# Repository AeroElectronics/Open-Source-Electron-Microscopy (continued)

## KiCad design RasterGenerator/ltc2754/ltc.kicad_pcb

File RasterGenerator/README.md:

The raster generator is based on the LTC2754. It is a quad channel multiplying current output DAC with impressive specifications. My (as of yet untested) idea is to use two of the channels to create raster patterns and use the other two channels to attenuate those signals using the multiplying functionality. Ideally, this should provide attenuation and improve dynamic range, but it remains to be seen how well this will work, especially at high speeds. More to come.

I would hole off on trying to replicate this work until I spend some more time seeing if its going to work well.

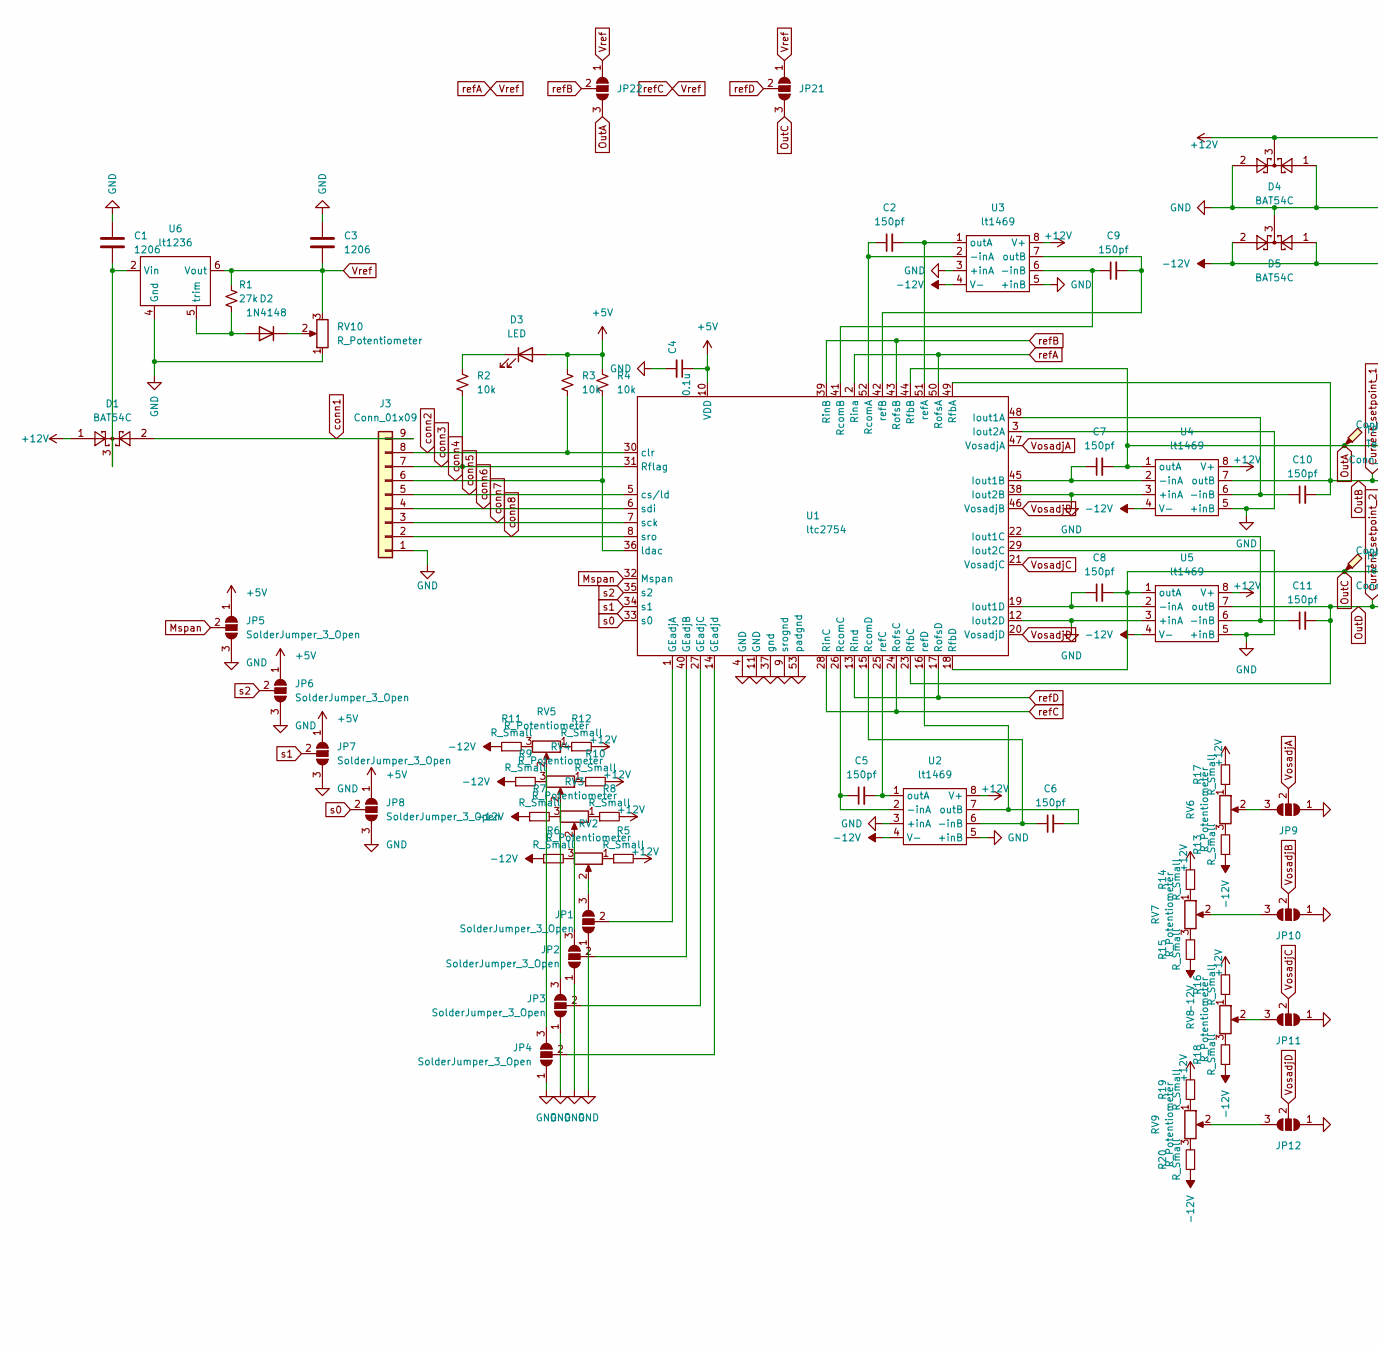
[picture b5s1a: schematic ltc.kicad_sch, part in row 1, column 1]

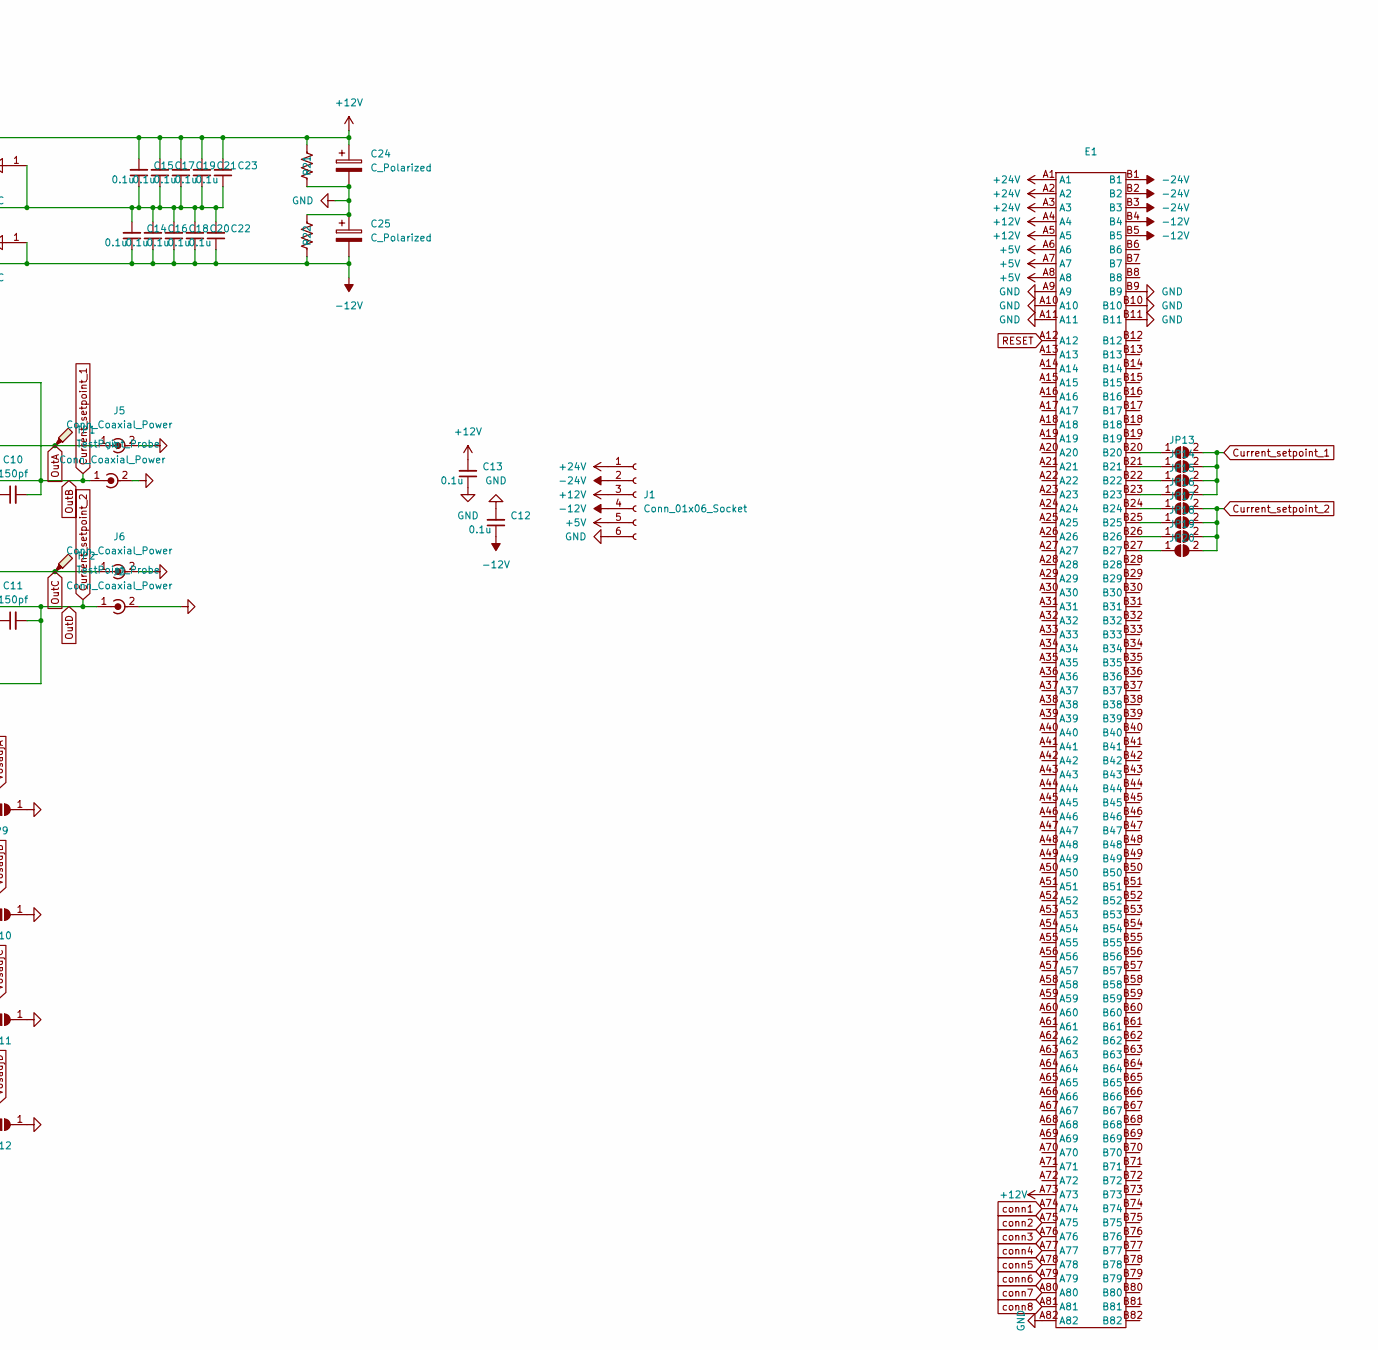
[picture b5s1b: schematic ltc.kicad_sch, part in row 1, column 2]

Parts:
C1, C3: 1206; C_1206_3216Metric
C2, C5, C6, C7, C8, C9, C10, C11: 150pf; C_0603_1608Metric_Pad1.08x0.95mm_HandSolder
C4, C12, C13, C14, C15, C16, C17, C18, C19, C20, C21, C22, C23: 0.1u; C_1206_3216Metric
C24, C25: C_Polarized; CP_Radial_D10.0mm_P5.00mm
D1, D4, D5: BAT54C; SOT-23
D2: 1N4148; D_SOD-323_HandSoldering
D3: LED; LED_0201_0603Metric_Pad0.64x0.40mm_HandSolder
E1: BUS_PCIexpress_x16
J1: Conn_01x06_Socket; PhoenixContact_MC_1,5_6-GF-3.81_1x06_P3.81mm_Horizontal_Thr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
J2, J4: Conn_Coaxial_Power; BNC_Amphenol_B6252HB-NPP3G-50_Horizontal
J3: Conn_01x09; PinHeader_1x09_P2.54mm_Vertical
J5, J6: Conn_Coaxial_Power; U.FL_Molex_MCRF_73412-0110_Vertical
JP1, JP2, JP3, JP4, JP5, JP6, JP7, JP8, JP9, JP10, JP11, JP12, JP21, JP22: SolderJumper_3_Open; SolderJumper-3_P1.3mm_Open_RoundedPad1.0x1.5mm
JP13, JP14, JP15, JP16, JP17, JP18, JP19, JP20: SolderJumper_2_Open; SolderJumper-2_P1.3mm_Open_RoundedPad1.0x1.5mm
R1: 27k; R_0603_1608Metric_Pad0.98x0.95mm_HandSolder
R2, R3, R4: 10k; R_0603_1608Metric_Pad0.98x0.95mm_HandSolder
R5, R6, R7, R8, R9, R10, R11, R12, R13, R14, R15, R16, R17, R18, R19, R20: R_Small; R_0603_1608Metric_Pad0.98x0.95mm_HandSolder
R21, R22: 100k; R_0603_1608Metric_Pad0.98x0.95mm_HandSolder
RV2, RV3, RV4, RV5, RV6, RV7, RV8, RV9, RV10: R_Potentiometer; Potentiometer_Bourns_3296W_Vertical
TP1, TP2: TestPoint_Probe; PinHeader_1x01_P2.54mm_Vertical
U1: ltc2754; LTC2754BCUKG-16-PBF
U2, U3, U4, U5: lt1469; LT1469IS8-PBF
U6: lt1236; SOIC-8_3.9x4.9mm_P1.27mm

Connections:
+5V: C4.1, D3.2 (A), E1.A6, E1.A7, E1.A8, J1.5, JP5.1 (A), JP6.1 (A), JP7.1 (A), JP8.1 (A), R3.1, R4.1, U1.10 (VDD)
+12V: C13.2, C15.2, C17.2, C19.2, C21.2, C23.2, C24.1, D1.1, D4.3, E1.A4, E1.A5, E1.A73, J1.3, R5.2, R8.2, R10.2, R12.2, R14.2, R16.2, R17.2, R19.2, R21.2, U2.8 (V+), U3.8 (V+), U4.8 (V+), U5.8 (V+)
+24V: E1.A1, E1.A2, E1.A3, J1.1
-12V: C12.1, C14.1, C16.1, C18.1, C20.1, C22.1, C25.2, D5.1, D5.2, E1.B4, E1.B5, J1.4, R6.1, R7.1, R9.1, R11.1, R13.1, R15.1, R18.1, R20.1, R22.1, U2.4 (V-), U3.4 (V-), U4.4 (V-), U5.4 (V-)
-24V: E1.B1, E1.B2, E1.B3, J1.2
Current_setpoint_1: C10.2, J4.1 (In), JP13.2 (B), JP14.2 (B), JP15.2 (B), JP16.2 (B), U1.49 (RfbA), U4.7 (outB)
Current_setpoint_2: C11.2, J2.1 (In), JP17.2 (B), JP18.2 (B), JP19.2 (B), JP20.2 (B), U1.23 (RfbC), U5.7 (outB)
GND: C1.2, C3.2, C4.2, C12.2, C13.1, C14.2, C15.1, C16.2, C17.1, C18.2, C19.1, C20.2, C21.1, C22.2, C23.1, C24.2, C25.1, D4.1, D4.2, D5.3, E1.A9, E1.A10, E1.A11, E1.A82, E1.B9, E1.B10, E1.B11, J1.6, J2.2 (Ext), J3.1, J4.2 (Ext), J5.2 (Ext), J6.2 (Ext), JP1.1 (A), JP2.1 (A), JP3.1 (A), JP4.1 (A), JP5.3 (B), JP6.3 (B), JP7.3 (B), JP8.3 (B), JP9.1 (A), JP10.1 (A), JP11.1 (A), JP12.1 (A), R21.1, R22.2, RV10.1, U1.3 (Iout2A), U1.4 (GND), U1.9 (srognd), U1.11 (GND), U1.12 (Iout2D), U1.29 (Iout2C), U1.37 (gnd), U1.38 (Iout2B), U1.53 (padgnd), U2.3 (+inA), U2.5 (+inB), U3.3 (+inA), U3.5 (+inB), U4.3 (+inA), U4.5 (+inB), U5.3 (+inA), U5.5 (+inB), U6.4 (Gnd)
Mspan: JP5.2 (C), U1.32 (Mspan)
unnamed: D2.2 (A), R1.2, U6.5 (trim)
unnamed: D2.1 (K), RV10.2
unnamed: D3.1 (K), R2.1
unnamed: JP1.3 (B), RV2.2
unnamed: JP1.2 (C), U1.1 (GEadjA)
unnamed: JP2.3 (B), RV3.2
unnamed: JP2.2 (C), U1.40 (GEadjB)
unnamed: JP3.3 (B), RV4.2
unnamed: JP3.2 (C), U1.27 (GEadjC)
unnamed: JP4.3 (B), RV5.2
unnamed: JP4.2 (C), U1.14 (GEadjd)
unnamed: JP9.3 (B), RV6.2
unnamed: JP10.3 (B), RV7.2
unnamed: JP11.3 (B), RV8.2
unnamed: JP12.3 (B), RV9.2
unnamed: E1.B20, JP13.1 (A)
unnamed: E1.B21, JP14.1 (A)
unnamed: E1.B22, JP15.1 (A)
unnamed: E1.B23, JP16.1 (A)
unnamed: E1.B24, JP17.1 (A)
unnamed: E1.B25, JP18.1 (A)
unnamed: E1.B26, JP19.1 (A)
unnamed: E1.B27, JP20.1 (A)
unnamed: R5.1, RV2.1
unnamed: R6.2, RV2.3
unnamed: R7.2, RV3.3
unnamed: R8.1, RV3.1
unnamed: R9.2, RV4.3
unnamed: R10.1, RV4.1
unnamed: R11.2, RV5.3
unnamed: R12.1, RV5.1
unnamed: R13.2, RV6.3
unnamed: R14.1, RV7.1
unnamed: R15.2, RV7.3
unnamed: R16.1, RV8.1
unnamed: R17.1, RV6.1
unnamed: R18.2, RV8.3
unnamed: R19.1, RV9.1
unnamed: R20.2, RV9.3
unnamed: C10.1, U1.48 (Iout1A), U4.6 (-inB)
unnamed: C7.1, U1.45 (Iout1B), U4.2 (-inA)
unnamed: C11.1, U1.22 (Iout1C), U5.6 (-inB)
unnamed: C8.1, U1.19 (Iout1D), U5.2 (-inA)
unnamed: C2.1, U1.52 (RcomA), U3.2 (-inA)
unnamed: C9.1, U1.41 (RcomB), U3.6 (-inB)
unnamed: C5.1, U1.26 (RcomC), U2.2 (-inA)
unnamed: C6.1, U1.15 (RcomD), U2.6 (-inB)
unnamed: C2.2, U1.51 (refA), U3.1 (outA)
unnamed: C9.2, U1.42 (refB), U3.7 (outB)
unnamed: C5.2, U1.25 (refC), U2.1 (outA)
unnamed: C6.2, U1.16 (refD), U2.7 (outB)
unnamed: C1.1, D1.3, U6.2 (Vin)
OutA: C7.2, J5.1 (In), JP22.3 (B), TP1.1, U1.44 (RfbB), U4.1 (outA)
OutC: C8.2, J6.1 (In), JP21.3 (B), TP2.1, U1.18 (RfbD), U5.1 (outA)
RESET: E1.A12
VosadjA: JP9.2 (C), U1.47 (VosadjA)
VosadjB: JP10.2 (C), U1.46 (VosadjB)
VosadjC: JP11.2 (C), U1.21 (VosadjC)
VosadjD: JP12.2 (C), U1.20 (VosadjD)
Vref: C3.1, JP21.1 (A), JP22.1 (A), R1.1, RV10.3, U1.2 (Rina), U1.24 (RofsC), U1.28 (RinC), U1.50 (RofsA), U6.6 (Vout)
conn1: D1.2, E1.A74, J3.9
conn2: E1.A75, J3.8, R3.2, U1.30 (clr)
conn3: E1.A76, J3.7, R2.2, U1.31 (Rflag)
conn4: E1.A77, J3.6, R4.2, U1.36 (ldac)
conn5: E1.A78, J3.5, U1.5 (cs/ld)
conn6: E1.A79, J3.4, U1.6 (sdi)
conn7: E1.A80, J3.3, U1.7 (sck)
conn8: E1.A81, J3.2, U1.8 (sro)
refB: JP22.2 (C), U1.39 (RinB), U1.43 (RofsB)
refD: JP21.2 (C), U1.13 (Rind), U1.17 (RofsD)
s0: JP8.2 (C), U1.33 (s0)
s1: JP7.2 (C), U1.34 (s1)
s2: JP6.2 (C), U1.35 (s2)

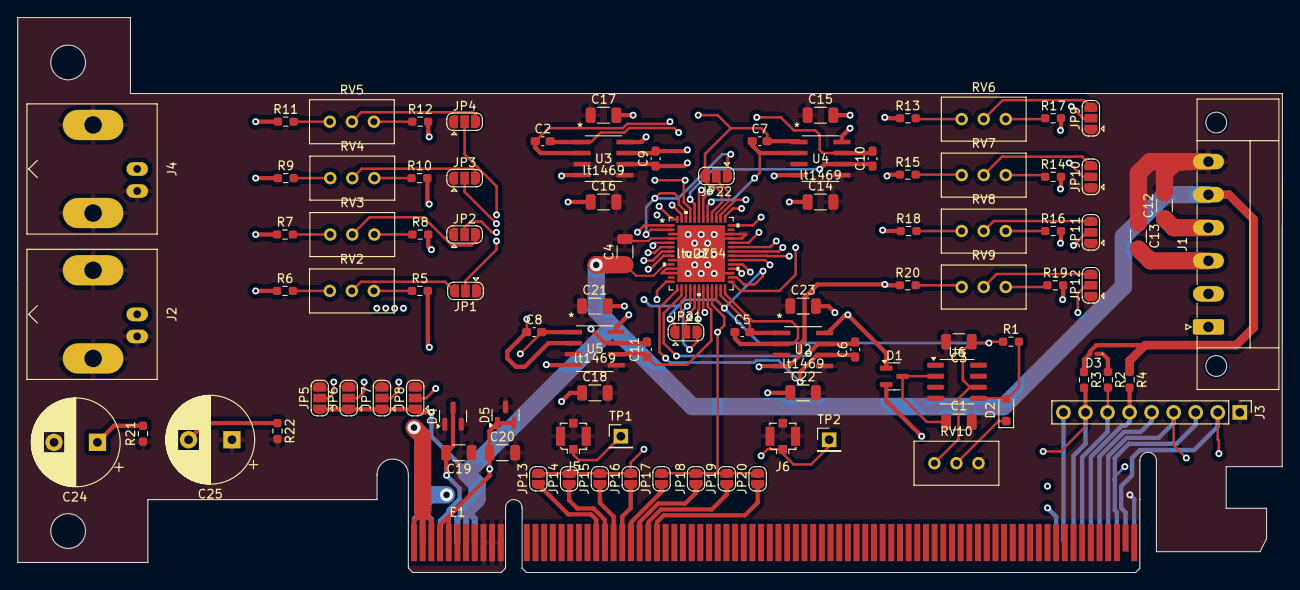
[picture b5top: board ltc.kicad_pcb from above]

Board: 4 copper layers, 145.8 x 64.0 mm, 98 parts (0 on the bottom side), 81 nets.

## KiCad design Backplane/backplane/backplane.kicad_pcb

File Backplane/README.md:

The backplane connects the various boards on the SEM control electronics. I have chosen to use a simple 'dumb' backplane which contains no electronics and simply connects the boards connectors together pin for pin.

I have also decided to use the PCIE X16 slot, because it is ubiquitous, capable, and low cost.

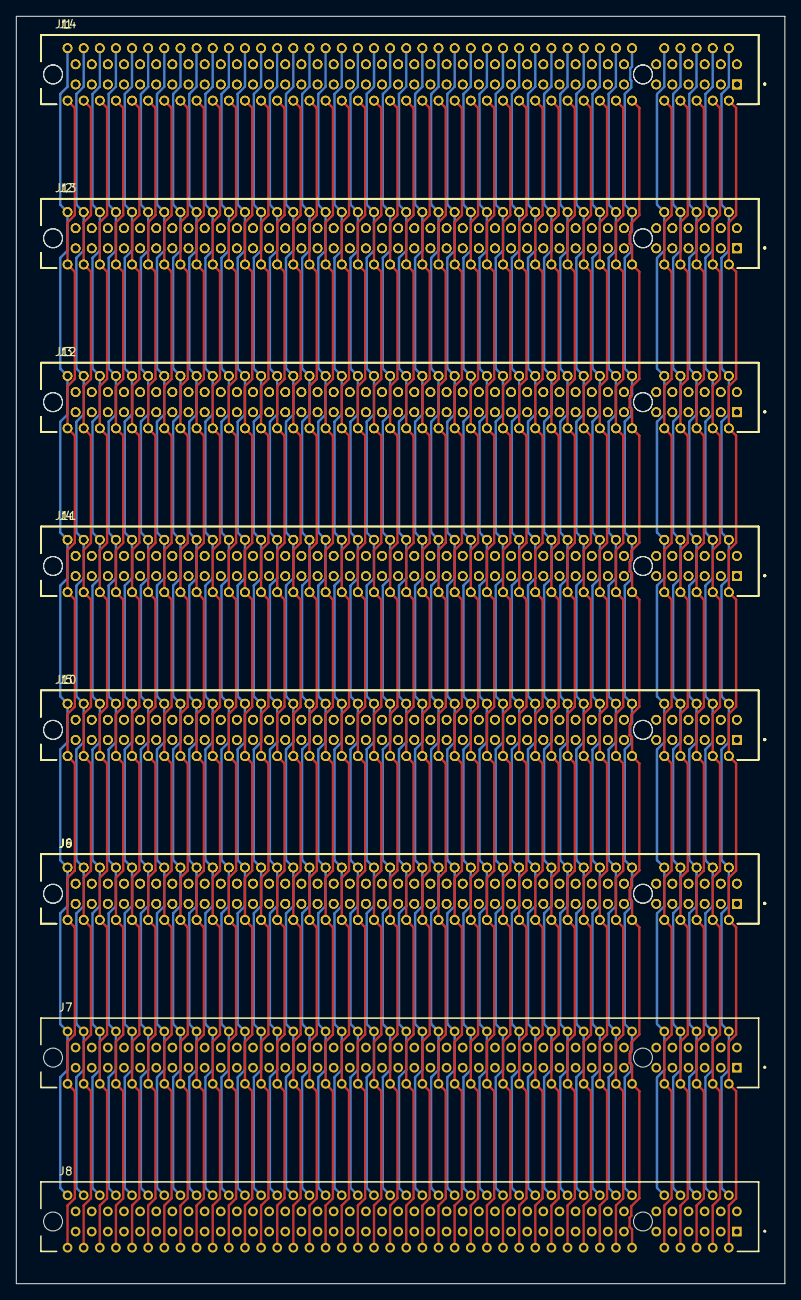
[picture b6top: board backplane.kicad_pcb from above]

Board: 4 copper layers, 95.3 x 157.1 mm, 14 parts (0 on the bottom side), 164 nets.

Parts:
J1, J2, J3, J4, J5, J6, J7, J8, J9, J10, J11, J12, J13, J14: PCIE-164-02-F-D-TH-TR; SAMTEC_PCIE-164-02-F-D-TH-TR

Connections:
A1: J1.A1, J2.A1, J3.A1, J4.A1, J5.A1, J6.A1, J7.A1, J8.A1, J9.A1, J10.A1, J11.A1, J12.A1, J13.A1, J14.A1
A2: J1.A2, J2.A2, J3.A2, J4.A2, J5.A2, J6.A2, J7.A2, J8.A2, J9.A2, J10.A2, J11.A2, J12.A2, J13.A2, J14.A2
A3: J1.A3, J2.A3, J3.A3, J4.A3, J5.A3, J6.A3, J7.A3, J8.A3, J9.A3, J10.A3, J11.A3, J12.A3, J13.A3, J14.A3
A4: J1.A4, J2.A4, J3.A4, J4.A4, J5.A4, J6.A4, J7.A4, J8.A4, J9.A4, J10.A4, J11.A4, J12.A4, J13.A4, J14.A4
A5: J1.A5, J2.A5, J3.A5, J4.A5, J5.A5, J6.A5, J7.A5, J8.A5, J9.A5, J10.A5, J11.A5, J12.A5, J13.A5, J14.A5
A6: J1.A6, J2.A6, J3.A6, J4.A6, J5.A6, J6.A6, J7.A6, J8.A6, J9.A6, J10.A6, J11.A6, J12.A6, J13.A6, J14.A6
A7: J1.A7, J2.A7, J3.A7, J4.A7, J5.A7, J6.A7, J7.A7, J8.A7, J9.A7, J10.A7, J11.A7, J12.A7, J13.A7, J14.A7
A8: J1.A8, J2.A8, J3.A8, J4.A8, J5.A8, J6.A8, J7.A8, J8.A8, J9.A8, J10.A8, J11.A8, J12.A8, J13.A8, J14.A8
A9: J1.A9, J2.A9, J3.A9, J4.A9, J5.A9, J6.A9, J7.A9, J8.A9, J9.A9, J10.A9, J11.A9, J12.A9, J13.A9, J14.A9
A10: J1.A10, J2.A10, J3.A10, J4.A10, J5.A10, J6.A10, J7.A10, J8.A10, J9.A10, J10.A10, J11.A10, J12.A10, J13.A10, J14.A10
A11: J1.A11, J2.A11, J3.A11, J4.A11, J5.A11, J6.A11, J7.A11, J8.A11, J9.A11, J10.A11, J11.A11, J12.A11, J13.A11, J14.A11
A12: J1.A12, J2.A12, J3.A12, J4.A12, J5.A12, J6.A12, J7.A12, J8.A12, J9.A12, J10.A12, J11.A12, J12.A12, J13.A12, J14.A12
A13: J1.A13, J2.A13, J3.A13, J4.A13, J5.A13, J6.A13, J7.A13, J8.A13, J9.A13, J10.A13, J11.A13, J12.A13, J13.A13, J14.A13
A14: J1.A14, J2.A14, J3.A14, J4.A14, J5.A14, J6.A14, J7.A14, J8.A14, J9.A14, J10.A14, J11.A14, J12.A14, J13.A14, J14.A14
A15: J1.A15, J2.A15, J3.A15, J4.A15, J5.A15, J6.A15, J7.A15, J8.A15, J9.A15, J10.A15, J11.A15, J12.A15, J13.A15, J14.A15
A16: J1.A16, J2.A16, J3.A16, J4.A16, J5.A16, J6.A16, J7.A16, J8.A16, J9.A16, J10.A16, J11.A16, J12.A16, J13.A16, J14.A16
A17: J1.A17, J2.A17, J3.A17, J4.A17, J5.A17, J6.A17, J7.A17, J8.A17, J9.A17, J10.A17, J11.A17, J12.A17, J13.A17, J14.A17
A18: J1.A18, J2.A18, J3.A18, J4.A18, J5.A18, J6.A18, J7.A18, J8.A18, J9.A18, J10.A18, J11.A18, J12.A18, J13.A18, J14.A18
A19: J1.A19, J2.A19, J3.A19, J4.A19, J5.A19, J6.A19, J7.A19, J8.A19, J9.A19, J10.A19, J11.A19, J12.A19, J13.A19, J14.A19
A20: J1.A20, J2.A20, J3.A20, J4.A20, J5.A20, J6.A20, J7.A20, J8.A20, J9.A20, J10.A20, J11.A20, J12.A20, J13.A20, J14.A20
A21: J1.A21, J2.A21, J3.A21, J4.A21, J5.A21, J6.A21, J7.A21, J8.A21, J9.A21, J10.A21, J11.A21, J12.A21, J13.A21, J14.A21
A22: J1.A22, J2.A22, J3.A22, J4.A22, J5.A22, J6.A22, J7.A22, J8.A22, J9.A22, J10.A22, J11.A22, J12.A22, J13.A22, J14.A22
A23: J1.A23, J2.A23, J3.A23, J4.A23, J5.A23, J6.A23, J7.A23, J8.A23, J9.A23, J10.A23, J11.A23, J12.A23, J13.A23, J14.A23
A24: J1.A24, J2.A24, J3.A24, J4.A24, J5.A24, J6.A24, J7.A24, J8.A24, J9.A24, J10.A24, J11.A24, J12.A24, J13.A24, J14.A24
A25: J1.A25, J2.A25, J3.A25, J4.A25, J5.A25, J6.A25, J7.A25, J8.A25, J9.A25, J10.A25, J11.A25, J12.A25, J13.A25, J14.A25
A26: J1.A26, J2.A26, J3.A26, J4.A26, J5.A26, J6.A26, J7.A26, J8.A26, J9.A26, J10.A26, J11.A26, J12.A26, J13.A26, J14.A26
A27: J1.A27, J2.A27, J3.A27, J4.A27, J5.A27, J6.A27, J7.A27, J8.A27, J9.A27, J10.A27, J11.A27, J12.A27, J13.A27, J14.A27
A28: J1.A28, J2.A28, J3.A28, J4.A28, J5.A28, J6.A28, J7.A28, J8.A28, J9.A28, J10.A28, J11.A28, J12.A28, J13.A28, J14.A28
A29: J1.A29, J2.A29, J3.A29, J4.A29, J5.A29, J6.A29, J7.A29, J8.A29, J9.A29, J10.A29, J11.A29, J12.A29, J13.A29, J14.A29
A30: J1.A30, J2.A30, J3.A30, J4.A30, J5.A30, J6.A30, J7.A30, J8.A30, J9.A30, J10.A30, J11.A30, J12.A30, J13.A30, J14.A30
A31: J1.A31, J2.A31, J3.A31, J4.A31, J5.A31, J6.A31, J7.A31, J8.A31, J9.A31, J10.A31, J11.A31, J12.A31, J13.A31, J14.A31
A32: J1.A32, J2.A32, J3.A32, J4.A32, J5.A32, J6.A32, J7.A32, J8.A32, J9.A32, J10.A32, J11.A32, J12.A32, J13.A32, J14.A32
A33: J1.A33, J2.A33, J3.A33, J4.A33, J5.A33, J6.A33, J7.A33, J8.A33, J9.A33, J10.A33, J11.A33, J12.A33, J13.A33, J14.A33
A34: J1.A34, J2.A34, J3.A34, J4.A34, J5.A34, J6.A34, J7.A34, J8.A34, J9.A34, J10.A34, J11.A34, J12.A34, J13.A34, J14.A34
A35: J1.A35, J2.A35, J3.A35, J4.A35, J5.A35, J6.A35, J7.A35, J8.A35, J9.A35, J10.A35, J11.A35, J12.A35, J13.A35, J14.A35
A36: J1.A36, J2.A36, J3.A36, J4.A36, J5.A36, J6.A36, J7.A36, J8.A36, J9.A36, J10.A36, J11.A36, J12.A36, J13.A36, J14.A36
A37: J1.A37, J2.A37, J3.A37, J4.A37, J5.A37, J6.A37, J7.A37, J8.A37, J9.A37, J10.A37, J11.A37, J12.A37, J13.A37, J14.A37
A38: J1.A38, J2.A38, J3.A38, J4.A38, J5.A38, J6.A38, J7.A38, J8.A38, J9.A38, J10.A38, J11.A38, J12.A38, J13.A38, J14.A38
A39: J1.A39, J2.A39, J3.A39, J4.A39, J5.A39, J6.A39, J7.A39, J8.A39, J9.A39, J10.A39, J11.A39, J12.A39, J13.A39, J14.A39
A40: J1.A40, J2.A40, J3.A40, J4.A40, J5.A40, J6.A40, J7.A40, J8.A40, J9.A40, J10.A40, J11.A40, J12.A40, J13.A40, J14.A40
A41: J1.A41, J2.A41, J3.A41, J4.A41, J5.A41, J6.A41, J7.A41, J8.A41, J9.A41, J10.A41, J11.A41, J12.A41, J13.A41, J14.A41
A42: J1.A42, J2.A42, J3.A42, J4.A42, J5.A42, J6.A42, J7.A42, J8.A42, J9.A42, J10.A42, J11.A42, J12.A42, J13.A42, J14.A42
A43: J1.A43, J2.A43, J3.A43, J4.A43, J5.A43, J6.A43, J7.A43, J8.A43, J9.A43, J10.A43, J11.A43, J12.A43, J13.A43, J14.A43
A44: J1.A44, J2.A44, J3.A44, J4.A44, J5.A44, J6.A44, J7.A44, J8.A44, J9.A44, J10.A44, J11.A44, J12.A44, J13.A44, J14.A44
A45: J1.A45, J2.A45, J3.A45, J4.A45, J5.A45, J6.A45, J7.A45, J8.A45, J9.A45, J10.A45, J11.A45, J12.A45, J13.A45, J14.A45
A46: J1.A46, J2.A46, J3.A46, J4.A46, J5.A46, J6.A46, J7.A46, J8.A46, J9.A46, J10.A46, J11.A46, J12.A46, J13.A46, J14.A46
A47: J1.A47, J2.A47, J3.A47, J4.A47, J5.A47, J6.A47, J7.A47, J8.A47, J9.A47, J10.A47, J11.A47, J12.A47, J13.A47, J14.A47
A48: J1.A48, J2.A48, J3.A48, J4.A48, J5.A48, J6.A48, J7.A48, J8.A48, J9.A48, J10.A48, J11.A48, J12.A48, J13.A48, J14.A48
A49: J1.A49, J2.A49, J3.A49, J4.A49, J5.A49, J6.A49, J7.A49, J8.A49, J9.A49, J10.A49, J11.A49, J12.A49, J13.A49, J14.A49
A50: J1.A50, J2.A50, J3.A50, J4.A50, J5.A50, J6.A50, J7.A50, J8.A50, J9.A50, J10.A50, J11.A50, J12.A50, J13.A50, J14.A50
A51: J1.A51, J2.A51, J3.A51, J4.A51, J5.A51, J6.A51, J7.A51, J8.A51, J9.A51, J10.A51, J11.A51, J12.A51, J13.A51, J14.A51
A52: J1.A52, J2.A52, J3.A52, J4.A52, J5.A52, J6.A52, J7.A52, J8.A52, J9.A52, J10.A52, J11.A52, J12.A52, J13.A52, J14.A52
A53: J1.A53, J2.A53, J3.A53, J4.A53, J5.A53, J6.A53, J7.A53, J8.A53, J9.A53, J10.A53, J11.A53, J12.A53, J13.A53, J14.A53
A54: J1.A54, J2.A54, J3.A54, J4.A54, J5.A54, J6.A54, J7.A54, J8.A54, J9.A54, J10.A54, J11.A54, J12.A54, J13.A54, J14.A54
A55: J1.A55, J2.A55, J3.A55, J4.A55, J5.A55, J6.A55, J7.A55, J8.A55, J9.A55, J10.A55, J11.A55, J12.A55, J13.A55, J14.A55
A56: J1.A56, J2.A56, J3.A56, J4.A56, J5.A56, J6.A56, J7.A56, J8.A56, J9.A56, J10.A56, J11.A56, J12.A56, J13.A56, J14.A56
A57: J1.A57, J2.A57, J3.A57, J4.A57, J5.A57, J6.A57, J7.A57, J8.A57, J9.A57, J10.A57, J11.A57, J12.A57, J13.A57, J14.A57
A58: J1.A58, J2.A58, J3.A58, J4.A58, J5.A58, J6.A58, J7.A58, J8.A58, J9.A58, J10.A58, J11.A58, J12.A58, J13.A58, J14.A58
A59: J1.A59, J2.A59, J3.A59, J4.A59, J5.A59, J6.A59, J7.A59, J8.A59, J9.A59, J10.A59, J11.A59, J12.A59, J13.A59, J14.A59
A60: J1.A60, J2.A60, J3.A60, J4.A60, J5.A60, J6.A60, J7.A60, J8.A60, J9.A60, J10.A60, J11.A60, J12.A60, J13.A60, J14.A60
A61: J1.A61, J2.A61, J3.A61, J4.A61, J5.A61, J6.A61, J7.A61, J8.A61, J9.A61, J10.A61, J11.A61, J12.A61, J13.A61, J14.A61
A62: J1.A62, J2.A62, J3.A62, J4.A62, J5.A62, J6.A62, J7.A62, J8.A62, J9.A62, J10.A62, J11.A62, J12.A62, J13.A62, J14.A62
A63: J1.A63, J2.A63, J3.A63, J4.A63, J5.A63, J6.A63, J7.A63, J8.A63, J9.A63, J10.A63, J11.A63, J12.A63, J13.A63, J14.A63
A64: J1.A64, J2.A64, J3.A64, J4.A64, J5.A64, J6.A64, J7.A64, J8.A64, J9.A64, J10.A64, J11.A64, J12.A64, J13.A64, J14.A64
A65: J1.A65, J2.A65, J3.A65, J4.A65, J5.A65, J6.A65, J7.A65, J8.A65, J9.A65, J10.A65, J11.A65, J12.A65, J13.A65, J14.A65
A66: J1.A66, J2.A66, J3.A66, J4.A66, J5.A66, J6.A66, J7.A66, J8.A66, J9.A66, J10.A66, J11.A66, J12.A66, J13.A66, J14.A66
A67: J1.A67, J2.A67, J3.A67, J4.A67, J5.A67, J6.A67, J7.A67, J8.A67, J9.A67, J10.A67, J11.A67, J12.A67, J13.A67, J14.A67
A68: J1.A68, J2.A68, J3.A68, J4.A68, J5.A68, J6.A68, J7.A68, J8.A68, J9.A68, J10.A68, J11.A68, J12.A68, J13.A68, J14.A68
A69: J1.A69, J2.A69, J3.A69, J4.A69, J5.A69, J6.A69, J7.A69, J8.A69, J9.A69, J10.A69, J11.A69, J12.A69, J13.A69, J14.A69
A70: J1.A70, J2.A70, J3.A70, J4.A70, J5.A70, J6.A70, J7.A70, J8.A70, J9.A70, J10.A70, J11.A70, J12.A70, J13.A70, J14.A70
A71: J1.A71, J2.A71, J3.A71, J4.A71, J5.A71, J6.A71, J7.A71, J8.A71, J9.A71, J10.A71, J11.A71, J12.A71, J13.A71, J14.A71
A72: J1.A72, J2.A72, J3.A72, J4.A72, J5.A72, J6.A72, J7.A72, J8.A72, J9.A72, J10.A72, J11.A72, J12.A72, J13.A72, J14.A72
A73: J1.A73, J2.A73, J3.A73, J4.A73, J5.A73, J6.A73, J7.A73, J8.A73, J9.A73, J10.A73, J11.A73, J12.A73, J13.A73, J14.A73
A74: J1.A74, J2.A74, J3.A74, J4.A74, J5.A74, J6.A74, J7.A74, J8.A74, J9.A74, J10.A74, J11.A74, J12.A74, J13.A74, J14.A74
A75: J1.A75, J2.A75, J3.A75, J4.A75, J5.A75, J6.A75, J7.A75, J8.A75, J9.A75, J10.A75, J11.A75, J12.A75, J13.A75, J14.A75
A76: J1.A76, J2.A76, J3.A76, J4.A76, J5.A76, J6.A76, J7.A76, J8.A76, J9.A76, J10.A76, J11.A76, J12.A76, J13.A76, J14.A76
A77: J1.A77, J2.A77, J3.A77, J4.A77, J5.A77, J6.A77, J7.A77, J8.A77, J9.A77, J10.A77, J11.A77, J12.A77, J13.A77, J14.A77
A78: J1.A78, J2.A78, J3.A78, J4.A78, J5.A78, J6.A78, J7.A78, J8.A78, J9.A78, J10.A78, J11.A78, J12.A78, J13.A78, J14.A78
A79: J1.A79, J2.A79, J3.A79, J4.A79, J5.A79, J6.A79, J7.A79, J8.A79, J9.A79, J10.A79, J11.A79, J12.A79, J13.A79, J14.A79
A80: J1.A80, J2.A80, J3.A80, J4.A80, J5.A80, J6.A80, J7.A80, J8.A80, J9.A80, J10.A80, J11.A80, J12.A80, J13.A80, J14.A80
A81: J1.A81, J2.A81, J3.A81, J4.A81, J5.A81, J6.A81, J7.A81, J8.A81, J9.A81, J10.A81, J11.A81, J12.A81, J13.A81, J14.A81
A82: J1.A82, J2.A82, J3.A82, J4.A82, J5.A82, J6.A82, J7.A82, J8.A82, J9.A82, J10.A82, J11.A82, J12.A82, J13.A82, J14.A82
B1: J1.B1, J2.B1, J3.B1, J4.B1, J5.B1, J6.B1, J7.B1, J8.B1, J9.B1, J10.B1, J11.B1, J12.B1, J13.B1, J14.B1
B2: J1.B2, J2.B2, J3.B2, J4.B2, J5.B2, J6.B2, J7.B2, J8.B2, J9.B2, J10.B2, J11.B2, J12.B2, J13.B2, J14.B2
B3: J1.B3, J2.B3, J3.B3, J4.B3, J5.B3, J6.B3, J7.B3, J8.B3, J9.B3, J10.B3, J11.B3, J12.B3, J13.B3, J14.B3
B4: J1.B4, J2.B4, J3.B4, J4.B4, J5.B4, J6.B4, J7.B4, J8.B4, J9.B4, J10.B4, J11.B4, J12.B4, J13.B4, J14.B4
B5: J1.B5, J2.B5, J3.B5, J4.B5, J5.B5, J6.B5, J7.B5, J8.B5, J9.B5, J10.B5, J11.B5, J12.B5, J13.B5, J14.B5
B6: J1.B6, J2.B6, J3.B6, J4.B6, J5.B6, J6.B6, J7.B6, J8.B6, J9.B6, J10.B6, J11.B6, J12.B6, J13.B6, J14.B6
B7: J1.B7, J2.B7, J3.B7, J4.B7, J5.B7, J6.B7, J7.B7, J8.B7, J9.B7, J10.B7, J11.B7, J12.B7, J13.B7, J14.B7
B8: J1.B8, J2.B8, J3.B8, J4.B8, J5.B8, J6.B8, J7.B8, J8.B8, J9.B8, J10.B8, J11.B8, J12.B8, J13.B8, J14.B8
B9: J1.B9, J2.B9, J3.B9, J4.B9, J5.B9, J6.B9, J7.B9, J8.B9, J9.B9, J10.B9, J11.B9, J12.B9, J13.B9, J14.B9
B10: J1.B10, J2.B10, J3.B10, J4.B10, J5.B10, J6.B10, J7.B10, J8.B10, J9.B10, J10.B10, J11.B10, J12.B10, J13.B10, J14.B10
B11: J1.B11, J2.B11, J3.B11, J4.B11, J5.B11, J6.B11, J7.B11, J8.B11, J9.B11, J10.B11, J11.B11, J12.B11, J13.B11, J14.B11
B12: J1.B12, J2.B12, J3.B12, J4.B12, J5.B12, J6.B12, J7.B12, J8.B12, J9.B12, J10.B12, J11.B12, J12.B12, J13.B12, J14.B12
B13: J1.B13, J2.B13, J3.B13, J4.B13, J5.B13, J6.B13, J7.B13, J8.B13, J9.B13, J10.B13, J11.B13, J12.B13, J13.B13, J14.B13
B14: J1.B14, J2.B14, J3.B14, J4.B14, J5.B14, J6.B14, J7.B14, J8.B14, J9.B14, J10.B14, J11.B14, J12.B14, J13.B14, J14.B14
B15: J1.B15, J2.B15, J3.B15, J4.B15, J5.B15, J6.B15, J7.B15, J8.B15, J9.B15, J10.B15, J11.B15, J12.B15, J13.B15, J14.B15
B16: J1.B16, J2.B16, J3.B16, J4.B16, J5.B16, J6.B16, J7.B16, J8.B16, J9.B16, J10.B16, J11.B16, J12.B16, J13.B16, J14.B16
B17: J1.B17, J2.B17, J3.B17, J4.B17, J5.B17, J6.B17, J7.B17, J8.B17, J9.B17, J10.B17, J11.B17, J12.B17, J13.B17, J14.B17
B18: J1.B18, J2.B18, J3.B18, J4.B18, J5.B18, J6.B18, J7.B18, J8.B18, J9.B18, J10.B18, J11.B18, J12.B18, J13.B18, J14.B18
B19: J1.B19, J2.B19, J3.B19, J4.B19, J5.B19, J6.B19, J7.B19, J8.B19, J9.B19, J10.B19, J11.B19, J12.B19, J13.B19, J14.B19
B20: J1.B20, J2.B20, J3.B20, J4.B20, J5.B20, J6.B20, J7.B20, J8.B20, J9.B20, J10.B20, J11.B20, J12.B20, J13.B20, J14.B20
B21: J1.B21, J2.B21, J3.B21, J4.B21, J5.B21, J6.B21, J7.B21, J8.B21, J9.B21, J10.B21, J11.B21, J12.B21, J13.B21, J14.B21
B22: J1.B22, J2.B22, J3.B22, J4.B22, J5.B22, J6.B22, J7.B22, J8.B22, J9.B22, J10.B22, J11.B22, J12.B22, J13.B22, J14.B22
B23: J1.B23, J2.B23, J3.B23, J4.B23, J5.B23, J6.B23, J7.B23, J8.B23, J9.B23, J10.B23, J11.B23, J12.B23, J13.B23, J14.B23
B24: J1.B24, J2.B24, J3.B24, J4.B24, J5.B24, J6.B24, J7.B24, J8.B24, J9.B24, J10.B24, J11.B24, J12.B24, J13.B24, J14.B24
B25: J1.B25, J2.B25, J3.B25, J4.B25, J5.B25, J6.B25, J7.B25, J8.B25, J9.B25, J10.B25, J11.B25, J12.B25, J13.B25, J14.B25
B26: J1.B26, J2.B26, J3.B26, J4.B26, J5.B26, J6.B26, J7.B26, J8.B26, J9.B26, J10.B26, J11.B26, J12.B26, J13.B26, J14.B26
B27: J1.B27, J2.B27, J3.B27, J4.B27, J5.B27, J6.B27, J7.B27, J8.B27, J9.B27, J10.B27, J11.B27, J12.B27, J13.B27, J14.B27
B28: J1.B28, J2.B28, J3.B28, J4.B28, J5.B28, J6.B28, J7.B28, J8.B28, J9.B28, J10.B28, J11.B28, J12.B28, J13.B28, J14.B28
B29: J1.B29, J2.B29, J3.B29, J4.B29, J5.B29, J6.B29, J7.B29, J8.B29, J9.B29, J10.B29, J11.B29, J12.B29, J13.B29, J14.B29
B30: J1.B30, J2.B30, J3.B30, J4.B30, J5.B30, J6.B30, J7.B30, J8.B30, J9.B30, J10.B30, J11.B30, J12.B30, J13.B30, J14.B30
B31: J1.B31, J2.B31, J3.B31, J4.B31, J5.B31, J6.B31, J7.B31, J8.B31, J9.B31, J10.B31, J11.B31, J12.B31, J13.B31, J14.B31
B32: J1.B32, J2.B32, J3.B32, J4.B32, J5.B32, J6.B32, J7.B32, J8.B32, J9.B32, J10.B32, J11.B32, J12.B32, J13.B32, J14.B32
B33: J1.B33, J2.B33, J3.B33, J4.B33, J5.B33, J6.B33, J7.B33, J8.B33, J9.B33, J10.B33, J11.B33, J12.B33, J13.B33, J14.B33
B34: J1.B34, J2.B34, J3.B34, J4.B34, J5.B34, J6.B34, J7.B34, J8.B34, J9.B34, J10.B34, J11.B34, J12.B34, J13.B34, J14.B34
B35: J1.B35, J2.B35, J3.B35, J4.B35, J5.B35, J6.B35, J7.B35, J8.B35, J9.B35, J10.B35, J11.B35, J12.B35, J13.B35, J14.B35
B36: J1.B36, J2.B36, J3.B36, J4.B36, J5.B36, J6.B36, J7.B36, J8.B36, J9.B36, J10.B36, J11.B36, J12.B36, J13.B36, J14.B36
B37: J1.B37, J2.B37, J3.B37, J4.B37, J5.B37, J6.B37, J7.B37, J8.B37, J9.B37, J10.B37, J11.B37, J12.B37, J13.B37, J14.B37
B38: J1.B38, J2.B38, J3.B38, J4.B38, J5.B38, J6.B38, J7.B38, J8.B38, J9.B38, J10.B38, J11.B38, J12.B38, J13.B38, J14.B38
B39: J1.B39, J2.B39, J3.B39, J4.B39, J5.B39, J6.B39, J7.B39, J8.B39, J9.B39, J10.B39, J11.B39, J12.B39, J13.B39, J14.B39
B40: J1.B40, J2.B40, J3.B40, J4.B40, J5.B40, J6.B40, J7.B40, J8.B40, J9.B40, J10.B40, J11.B40, J12.B40, J13.B40, J14.B40
B41: J1.B41, J2.B41, J3.B41, J4.B41, J5.B41, J6.B41, J7.B41, J8.B41, J9.B41, J10.B41, J11.B41, J12.B41, J13.B41, J14.B41
B42: J1.B42, J2.B42, J3.B42, J4.B42, J5.B42, J6.B42, J7.B42, J8.B42, J9.B42, J10.B42, J11.B42, J12.B42, J13.B42, J14.B42
B43: J1.B43, J2.B43, J3.B43, J4.B43, J5.B43, J6.B43, J7.B43, J8.B43, J9.B43, J10.B43, J11.B43, J12.B43, J13.B43, J14.B43
B44: J1.B44, J2.B44, J3.B44, J4.B44, J5.B44, J6.B44, J7.B44, J8.B44, J9.B44, J10.B44, J11.B44, J12.B44, J13.B44, J14.B44
B45: J1.B45, J2.B45, J3.B45, J4.B45, J5.B45, J6.B45, J7.B45, J8.B45, J9.B45, J10.B45, J11.B45, J12.B45, J13.B45, J14.B45
B46: J1.B46, J2.B46, J3.B46, J4.B46, J5.B46, J6.B46, J7.B46, J8.B46, J9.B46, J10.B46, J11.B46, J12.B46, J13.B46, J14.B46
B47: J1.B47, J2.B47, J3.B47, J4.B47, J5.B47, J6.B47, J7.B47, J8.B47, J9.B47, J10.B47, J11.B47, J12.B47, J13.B47, J14.B47
B48: J1.B48, J2.B48, J3.B48, J4.B48, J5.B48, J6.B48, J7.B48, J8.B48, J9.B48, J10.B48, J11.B48, J12.B48, J13.B48, J14.B48
B49: J1.B49, J2.B49, J3.B49, J4.B49, J5.B49, J6.B49, J7.B49, J8.B49, J9.B49, J10.B49, J11.B49, J12.B49, J13.B49, J14.B49
B50: J1.B50, J2.B50, J3.B50, J4.B50, J5.B50, J6.B50, J7.B50, J8.B50, J9.B50, J10.B50, J11.B50, J12.B50, J13.B50, J14.B50
B51: J1.B51, J2.B51, J3.B51, J4.B51, J5.B51, J6.B51, J7.B51, J8.B51, J9.B51, J10.B51, J11.B51, J12.B51, J13.B51, J14.B51
B52: J1.B52, J2.B52, J3.B52, J4.B52, J5.B52, J6.B52, J7.B52, J8.B52, J9.B52, J10.B52, J11.B52, J12.B52, J13.B52, J14.B52
B53: J1.B53, J2.B53, J3.B53, J4.B53, J5.B53, J6.B53, J7.B53, J8.B53, J9.B53, J10.B53, J11.B53, J12.B53, J13.B53, J14.B53
B54: J1.B54, J2.B54, J3.B54, J4.B54, J5.B54, J6.B54, J7.B54, J8.B54, J9.B54, J10.B54, J11.B54, J12.B54, J13.B54, J14.B54
B55: J1.B55, J2.B55, J3.B55, J4.B55, J5.B55, J6.B55, J7.B55, J8.B55, J9.B55, J10.B55, J11.B55, J12.B55, J13.B55, J14.B55
B56: J1.B56, J2.B56, J3.B56, J4.B56, J5.B56, J6.B56, J7.B56, J8.B56, J9.B56, J10.B56, J11.B56, J12.B56, J13.B56, J14.B56
B57: J1.B57, J2.B57, J3.B57, J4.B57, J5.B57, J6.B57, J7.B57, J8.B57, J9.B57, J10.B57, J11.B57, J12.B57, J13.B57, J14.B57
B58: J1.B58, J2.B58, J3.B58, J4.B58, J5.B58, J6.B58, J7.B58, J8.B58, J9.B58, J10.B58, J11.B58, J12.B58, J13.B58, J14.B58
B59: J1.B59, J2.B59, J3.B59, J4.B59, J5.B59, J6.B59, J7.B59, J8.B59, J9.B59, J10.B59, J11.B59, J12.B59, J13.B59, J14.B59
B60: J1.B60, J2.B60, J3.B60, J4.B60, J5.B60, J6.B60, J7.B60, J8.B60, J9.B60, J10.B60, J11.B60, J12.B60, J13.B60, J14.B60
B61: J1.B61, J2.B61, J3.B61, J4.B61, J5.B61, J6.B61, J7.B61, J8.B61, J9.B61, J10.B61, J11.B61, J12.B61, J13.B61, J14.B61
B62: J1.B62, J2.B62, J3.B62, J4.B62, J5.B62, J6.B62, J7.B62, J8.B62, J9.B62, J10.B62, J11.B62, J12.B62, J13.B62, J14.B62
B63: J1.B63, J2.B63, J3.B63, J4.B63, J5.B63, J6.B63, J7.B63, J8.B63, J9.B63, J10.B63, J11.B63, J12.B63, J13.B63, J14.B63
B64: J1.B64, J2.B64, J3.B64, J4.B64, J5.B64, J6.B64, J7.B64, J8.B64, J9.B64, J10.B64, J11.B64, J12.B64, J13.B64, J14.B64
B65: J1.B65, J2.B65, J3.B65, J4.B65, J5.B65, J6.B65, J7.B65, J8.B65, J9.B65, J10.B65, J11.B65, J12.B65, J13.B65, J14.B65
B66: J1.B66, J2.B66, J3.B66, J4.B66, J5.B66, J6.B66, J7.B66, J8.B66, J9.B66, J10.B66, J11.B66, J12.B66, J13.B66, J14.B66
B67: J1.B67, J2.B67, J3.B67, J4.B67, J5.B67, J6.B67, J7.B67, J8.B67, J9.B67, J10.B67, J11.B67, J12.B67, J13.B67, J14.B67
B68: J1.B68, J2.B68, J3.B68, J4.B68, J5.B68, J6.B68, J7.B68, J8.B68, J9.B68, J10.B68, J11.B68, J12.B68, J13.B68, J14.B68
B69: J1.B69, J2.B69, J3.B69, J4.B69, J5.B69, J6.B69, J7.B69, J8.B69, J9.B69, J10.B69, J11.B69, J12.B69, J13.B69, J14.B69
B70: J1.B70, J2.B70, J3.B70, J4.B70, J5.B70, J6.B70, J7.B70, J8.B70, J9.B70, J10.B70, J11.B70, J12.B70, J13.B70, J14.B70
B71: J1.B71, J2.B71, J3.B71, J4.B71, J5.B71, J6.B71, J7.B71, J8.B71, J9.B71, J10.B71, J11.B71, J12.B71, J13.B71, J14.B71
B72: J1.B72, J2.B72, J3.B72, J4.B72, J5.B72, J6.B72, J7.B72, J8.B72, J9.B72, J10.B72, J11.B72, J12.B72, J13.B72, J14.B72
B73: J1.B73, J2.B73, J3.B73, J4.B73, J5.B73, J6.B73, J7.B73, J8.B73, J9.B73, J10.B73, J11.B73, J12.B73, J13.B73, J14.B73
B74: J1.B74, J2.B74, J3.B74, J4.B74, J5.B74, J6.B74, J7.B74, J8.B74, J9.B74, J10.B74, J11.B74, J12.B74, J13.B74, J14.B74
B75: J1.B75, J2.B75, J3.B75, J4.B75, J5.B75, J6.B75, J7.B75, J8.B75, J9.B75, J10.B75, J11.B75, J12.B75, J13.B75, J14.B75
B76: J1.B76, J2.B76, J3.B76, J4.B76, J5.B76, J6.B76, J7.B76, J8.B76, J9.B76, J10.B76, J11.B76, J12.B76, J13.B76, J14.B76
B77: J1.B77, J2.B77, J3.B77, J4.B77, J5.B77, J6.B77, J7.B77, J8.B77, J9.B77, J10.B77, J11.B77, J12.B77, J13.B77, J14.B77
B78: J1.B78, J2.B78, J3.B78, J4.B78, J5.B78, J6.B78, J7.B78, J8.B78, J9.B78, J10.B78, J11.B78, J12.B78, J13.B78, J14.B78
B79: J1.B79, J2.B79, J3.B79, J4.B79, J5.B79, J6.B79, J7.B79, J8.B79, J9.B79, J10.B79, J11.B79, J12.B79, J13.B79, J14.B79
B80: J1.B80, J2.B80, J3.B80, J4.B80, J5.B80, J6.B80, J7.B80, J8.B80, J9.B80, J10.B80, J11.B80, J12.B80, J13.B80, J14.B80
B81: J1.B81, J2.B81, J3.B81, J4.B81, J5.B81, J6.B81, J7.B81, J8.B81, J9.B81, J10.B81, J11.B81, J12.B81, J13.B81, J14.B81
B82: J1.B82, J2.B82, J3.B82, J4.B82, J5.B82, J6.B82, J7.B82, J8.B82, J9.B82, J10.B82, J11.B82, J12.B82, J13.B82, J14.B82

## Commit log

2025-01-20 Create LICENSE
2025-01-27 Create temp
2025-01-29 Create footprint_attribution
2025-01-29 opa541 footprint update
    moved opa541 footprint from snapmatic to kicad and custom symbol
2025-01-29 removing excess files
2025-01-29 Fixed footprint references
2025-01-29 temp
2025-10-15 Updates
    Updated to include both NC and NO solder jumpers for more options. Also added power LED. Also moved power connector closer to edge.
2025-10-15 update
    BOM update
2026-02-15 Revise design status descriptions in Design_Status.md
    Updated status descriptions for several designs, including the Single Ended Deflection Coil Driver and Adjustable Load.
2026-02-15 minor changes
2026-02-15 removed vacuum control board
2026-02-15 Remove Vacuum Control link from README
    Removed Vacuum Control section from README.
